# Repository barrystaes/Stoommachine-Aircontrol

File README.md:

# Stoommachine aircontrol
Stichting Stoommachine Oisterwijk 
http://destoommachine.nl/

# Licence
ISC

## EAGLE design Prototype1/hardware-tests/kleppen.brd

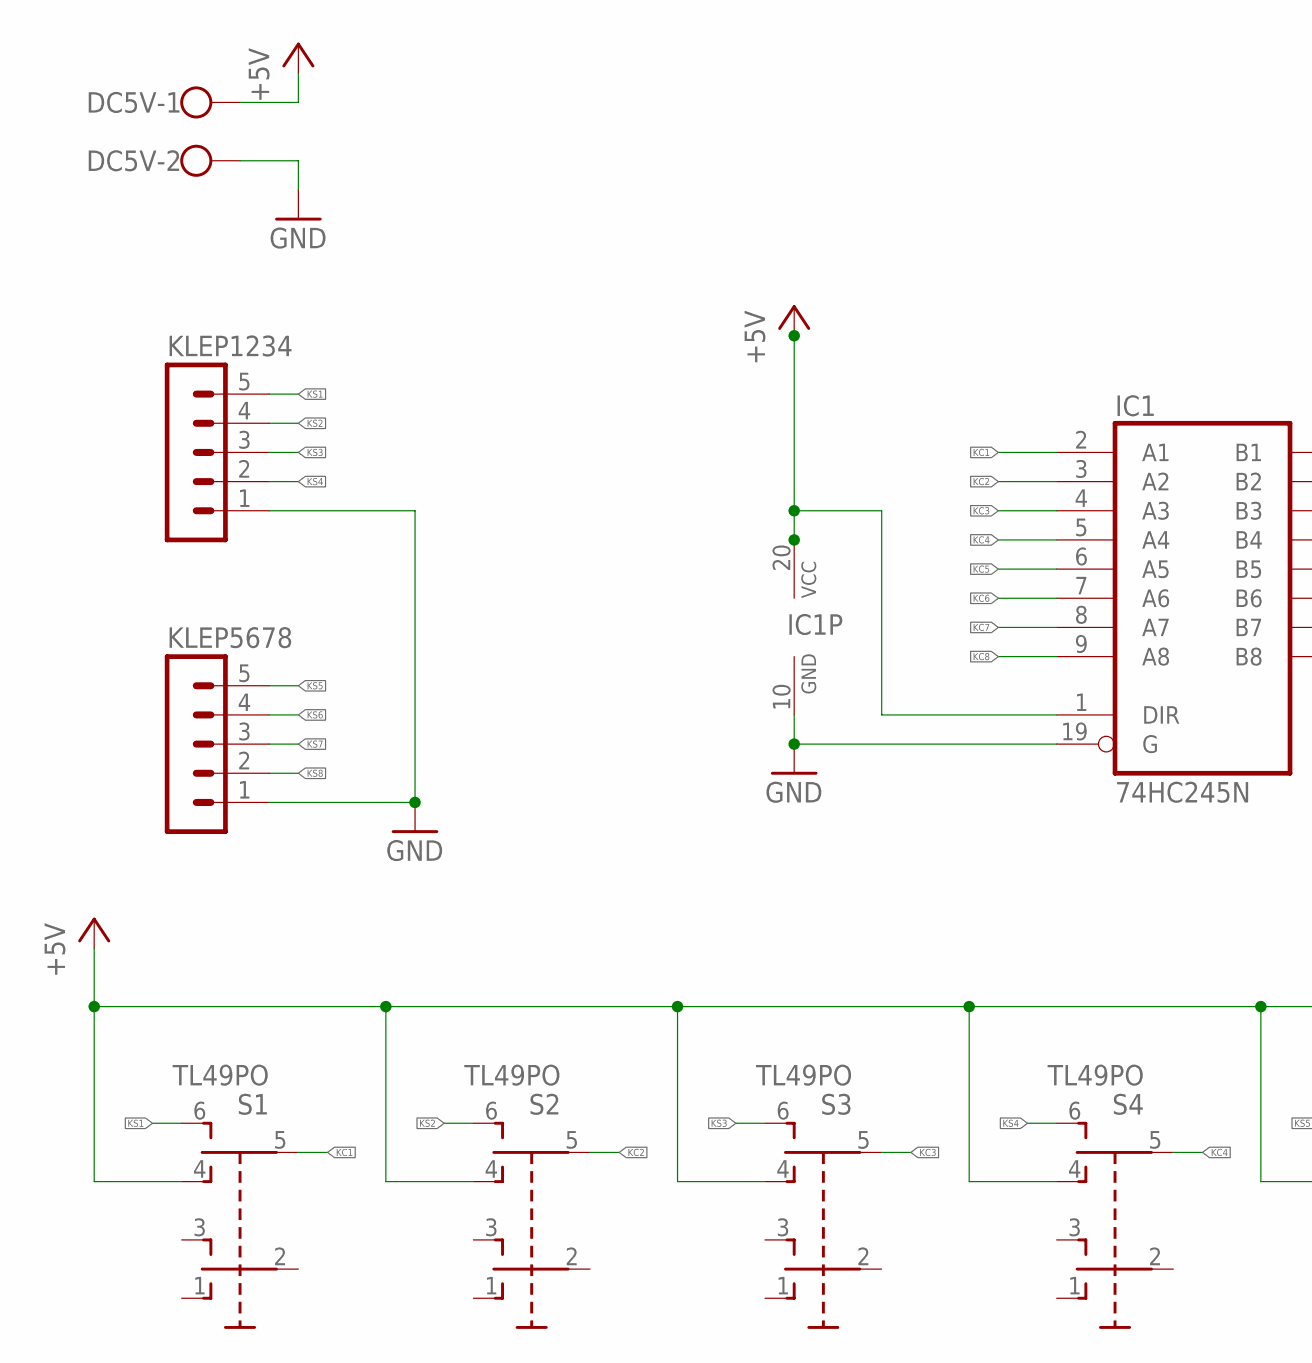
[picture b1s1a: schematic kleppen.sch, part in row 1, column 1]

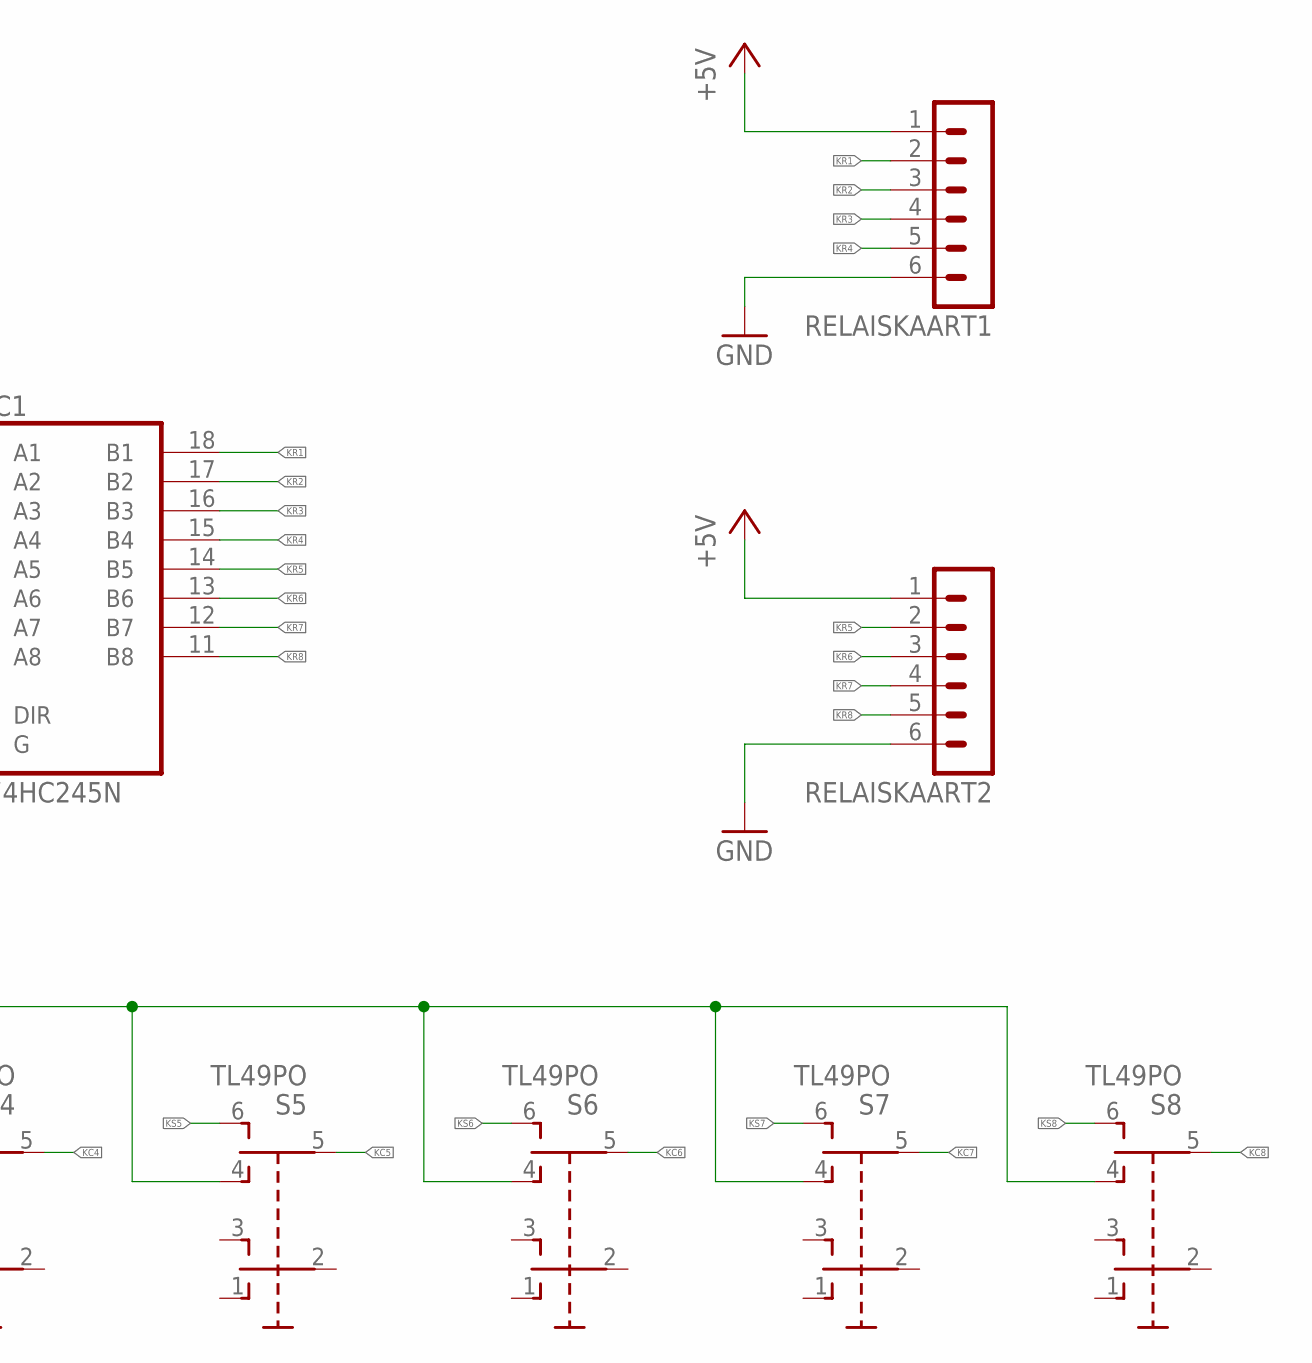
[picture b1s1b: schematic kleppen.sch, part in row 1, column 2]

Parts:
DC5V: W237-102
IC1: 74HC245N; DIL20
KLEP1234, KLEP5678: MA05-1
RELAISKAART1, RELAISKAART2: MA06-1
S1, S2, S3, S4, S5, S6, S7, S8: TL49PO; TL4XPO

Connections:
+5V: DC5V.1, IC1.1 (DIR), IC1.20 (VCC), RELAISKAART1.1, RELAISKAART2.1, S1.4 (O1), S2.4 (O1), S3.4 (O1), S4.4 (O1), S5.4 (O1), S6.4 (O1), S7.4 (O1), S8.4 (O1)
GND: DC5V.2, IC1.10 (GND), IC1.19 (G), RELAISKAART1.6, RELAISKAART2.6
KC1: IC1.2 (A1), S1.5 (P1)
KC2: IC1.3 (A2), S2.5 (P1)
KC3: IC1.4 (A3), S3.5 (P1)
KC4: IC1.5 (A4), S4.5 (P1)
KC5: IC1.6 (A5), S5.5 (P1)
KC6: IC1.7 (A6), S6.5 (P1)
KC7: IC1.8 (A7), S7.5 (P1)
KC8: IC1.9 (A8), S8.5 (P1)
KR1: IC1.18 (B1), RELAISKAART1.2
KR2: IC1.17 (B2), RELAISKAART1.3
KR3: IC1.16 (B3), RELAISKAART1.4
KR4: IC1.15 (B4), RELAISKAART1.5
KR5: IC1.14 (B5), RELAISKAART2.2
KR6: IC1.13 (B6), RELAISKAART2.3
KR7: IC1.12 (B7), RELAISKAART2.4
KR8: IC1.11 (B8), RELAISKAART2.5
KS1: KLEP1234.5, S1.6 (S1)
KS2: KLEP1234.4, S2.6 (S1)
KS3: KLEP1234.3, S3.6 (S1)
KS4: KLEP1234.2, S4.6 (S1)
KS5: KLEP5678.5, S5.6 (S1)
KS6: KLEP5678.4, S6.6 (S1)
KS7: KLEP5678.3, S7.6 (S1)
KS8: KLEP1234.1, KLEP5678.1, KLEP5678.2, S8.6 (S1)

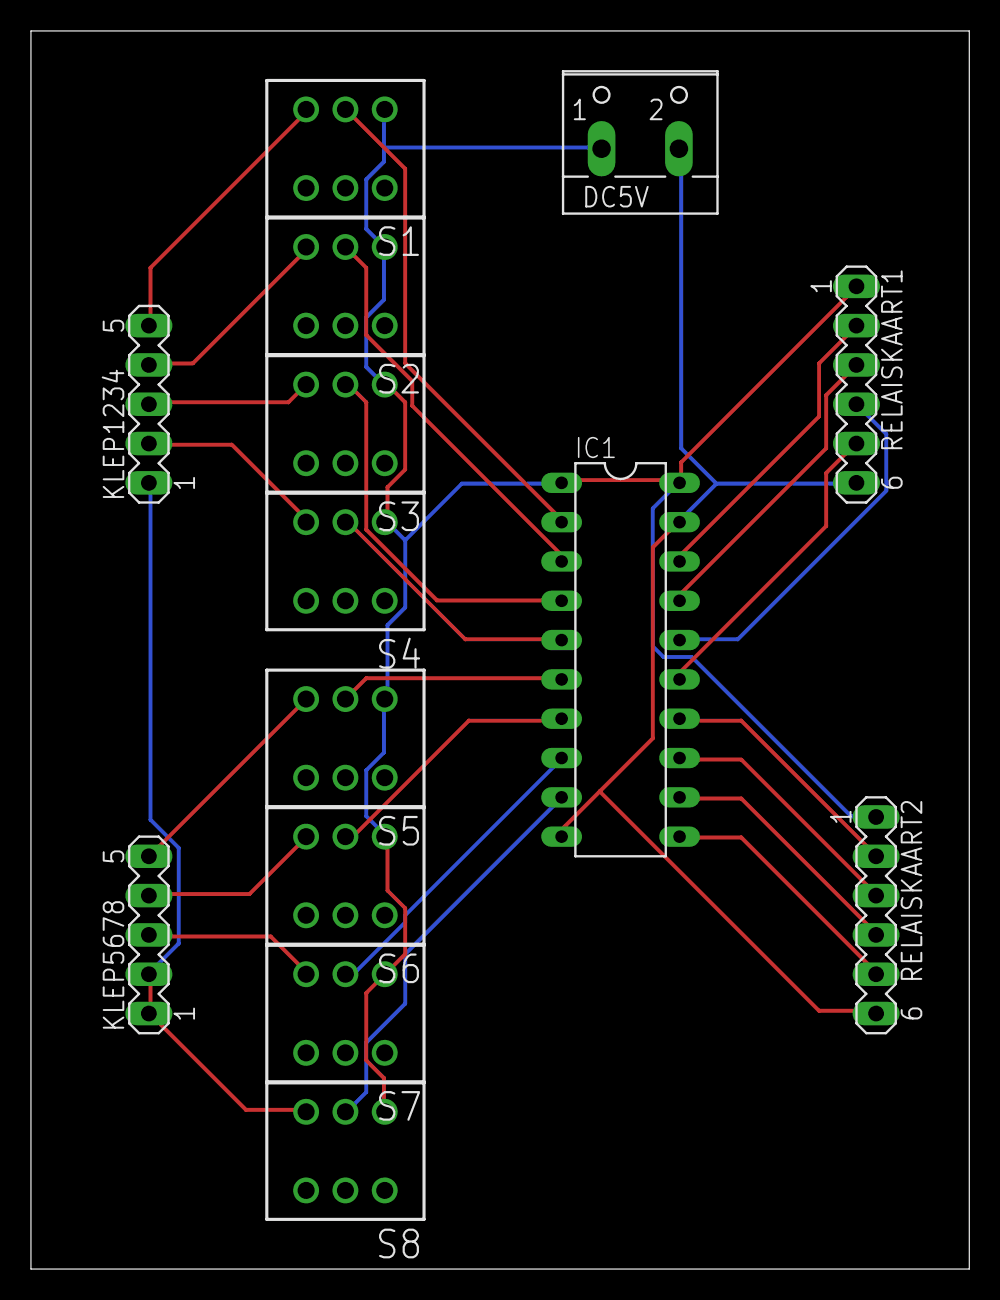
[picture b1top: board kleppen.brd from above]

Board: 2 copper layers, 60.6 x 80.0 mm, 14 parts (0 on the bottom side), 26 nets.

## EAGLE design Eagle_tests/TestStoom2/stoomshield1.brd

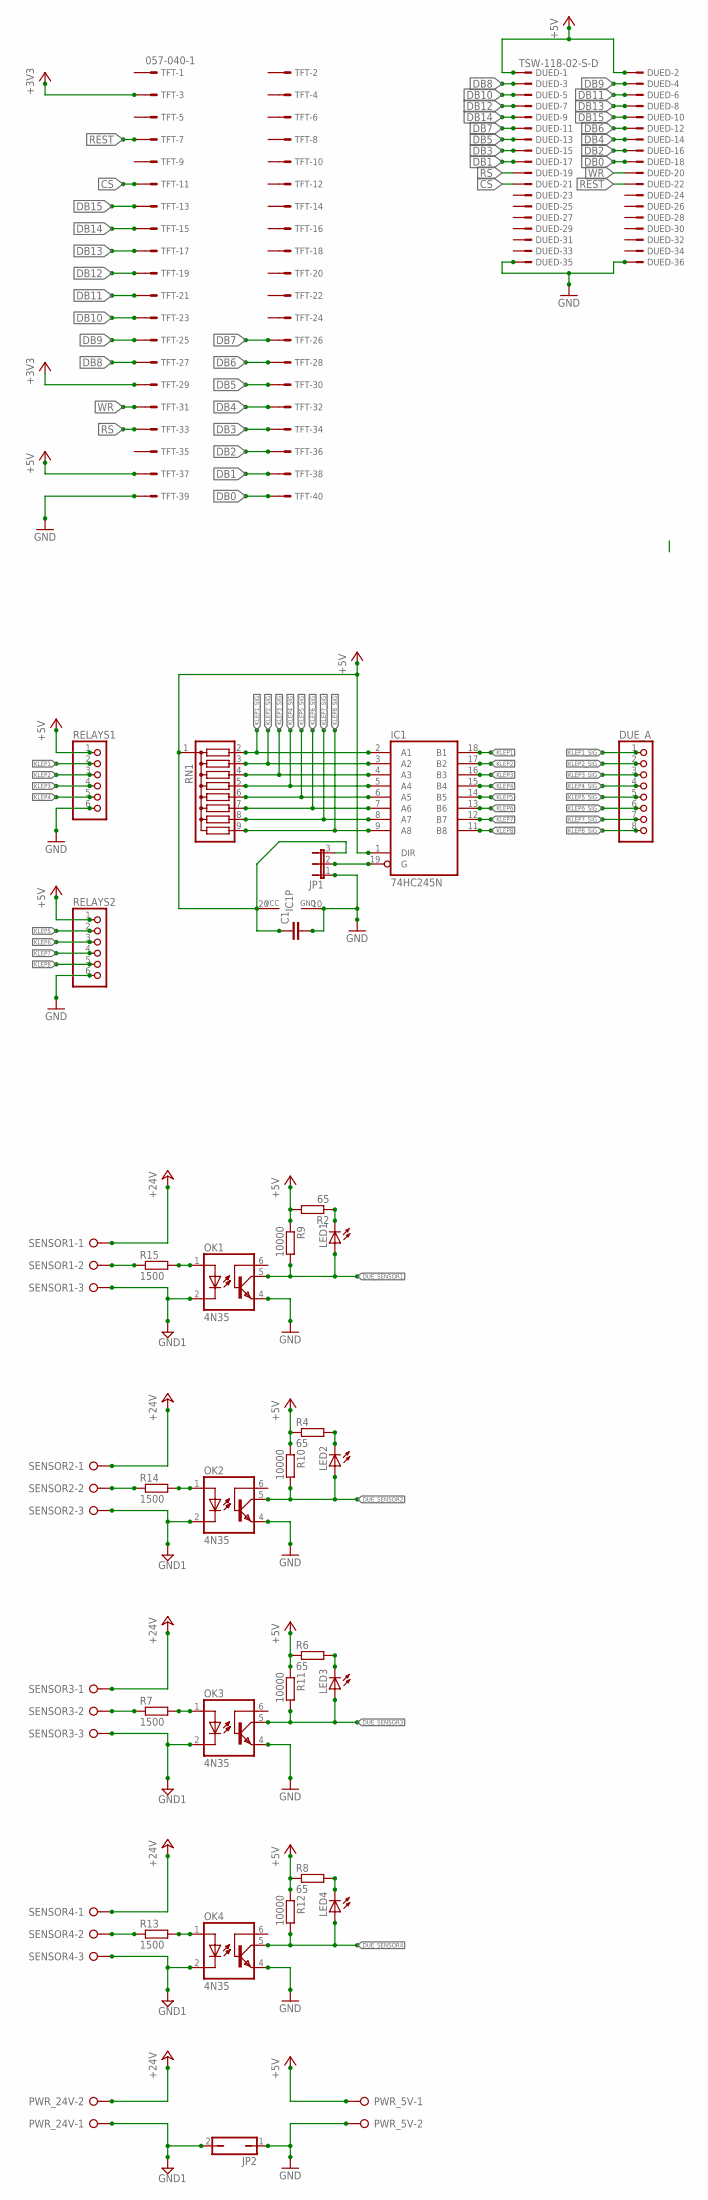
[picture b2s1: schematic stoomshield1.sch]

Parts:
C1: C-EU025-024X044; C025-024X044
DUED: TSW-118-02-S-D
DUE_A: PINHD-1X8; 1X08
IC1: 74HC245N; DIL20
JP1: JP2E; JP2
JP2: JP1Q; JP1
LED1, LED2, LED3, LED4: LED5MM
OK1, OK2, OK3, OK4: 4N35; DIL06
PWR_5V, PWR_24V: W237-02P; W237-132
R2, R4, R6, R8: 65; 0204/5
R7, R13, R14, R15: 1500; 0204/5
R9, R10, R11, R12: 10000; 0204/5
RELAYS1, RELAYS2: PINHD-1X6; 1X06
RN1: G08R; SIL9
SENSOR1, SENSOR2, SENSOR3, SENSOR4: W237-03P; W237-133
TFT: 057-040-1

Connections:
+5V: C1.1, DUED.1, DUED.2, IC1.1 (DIR), IC1.20 (VCC), JP1.3, PWR_5V.1, R2.2, R4.1, R6.1, R8.1, R9.1, R10.1, R11.1, R12.1, RELAYS1.1, RELAYS2.1, RN1.1, TFT.37
+24V: PWR_24V.2, SENSOR1.1, SENSOR2.1, SENSOR3.1, SENSOR4.1
CS: DUED.21, TFT.11
DB0: DUED.18, TFT.40
DB1: DUED.17, TFT.38
DB2: DUED.16, TFT.36
DB3: DUED.15, TFT.34
DB4: DUED.14, TFT.32
DB5: DUED.13, TFT.30
DB6: DUED.12, TFT.28
DB7: DUED.11, TFT.26
DB8: DUED.3, TFT.27
DB9: DUED.4, TFT.25
DB10: DUED.5, TFT.23
DB11: DUED.6, TFT.21
DB12: DUED.7, TFT.19
DB13: DUED.8, TFT.17
DB14: DUED.9, TFT.15
DB15: DUED.10, TFT.13
DUE_SENSOR1: LED1.A, OK1.5 (COL), R9.2
DUE_SENSOR2: LED2.A, OK2.5 (COL), R10.2
DUE_SENSOR3: LED3.A, OK3.5 (COL), R11.2
DUE_SENSOR4: LED4.A, OK4.5 (COL), R12.2
GND: C1.2, DUED.35, DUED.36, IC1.10 (GND), JP1.1, JP2.1, OK1.4 (EMI), OK2.4 (EMI), OK3.4 (EMI), OK4.4 (EMI), PWR_5V.2, RELAYS1.6, RELAYS2.6, TFT.39
GND1: JP2.2, OK1.2 (C), OK2.2 (C), OK3.2 (C), OK4.2 (C), PWR_24V.1, SENSOR1.3, SENSOR2.3, SENSOR3.3, SENSOR4.3
KLEP1: IC1.18 (B1), RELAYS1.2
KLEP1_SIG: DUE_A.1, IC1.2 (A1), RN1.2
KLEP2: IC1.17 (B2), RELAYS1.3
KLEP2_SIG: DUE_A.2, IC1.3 (A2), RN1.3
KLEP3: IC1.16 (B3), RELAYS1.4
KLEP3_SIG: DUE_A.3, IC1.4 (A3), RN1.4
KLEP4: IC1.15 (B4), RELAYS1.5
KLEP4_SIG: DUE_A.4, IC1.5 (A4), RN1.5
KLEP5: IC1.14 (B5), RELAYS2.2
KLEP5_SIG: DUE_A.5, IC1.6 (A5), RN1.6
KLEP6: IC1.13 (B6), RELAYS2.3
KLEP6_SIG: DUE_A.6, IC1.7 (A6), RN1.7
KLEP7: IC1.12 (B7), RELAYS2.4
KLEP7_SIG: DUE_A.7, IC1.8 (A7), RN1.8
KLEP8: IC1.11 (B8), RELAYS2.5
KLEP8_SIG: DUE_A.8, IC1.9 (A8), RN1.9
unnamed: IC1.19 (G), JP1.2
unnamed: R15.1, SENSOR1.2
unnamed: OK1.1 (A), R15.2
unnamed: LED1.K (C), R2.1
unnamed: OK2.1 (A), R14.2
unnamed: R14.1, SENSOR2.2
unnamed: LED2.K (C), R4.2
unnamed: OK3.1 (A), R7.2
unnamed: R7.1, SENSOR3.2
unnamed: LED3.K (C), R6.2
unnamed: OK4.1 (A), R13.2
unnamed: R13.1, SENSOR4.2
unnamed: LED4.K (C), R8.2
REST: DUED.22, TFT.7
RS: DUED.19, TFT.33
WR: DUED.20, TFT.31

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
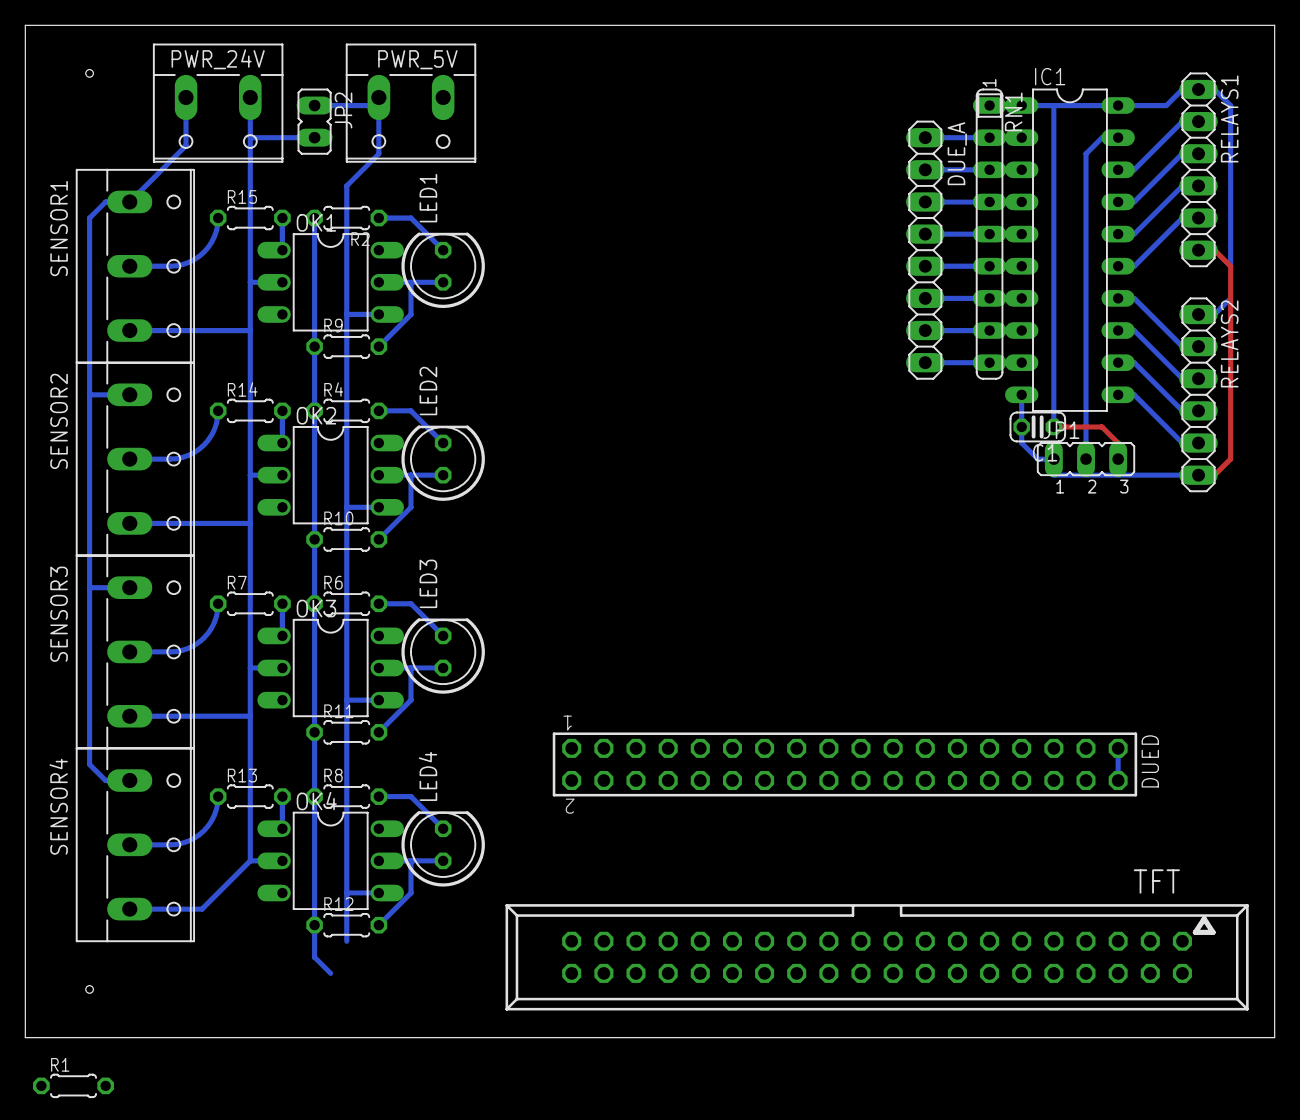
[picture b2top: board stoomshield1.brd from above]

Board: 2 copper layers, 98.7 x 80.0 mm, 37 parts (0 on the bottom side), 59 nets.

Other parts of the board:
R1: 10000; 0204/5

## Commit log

2015-02-08 Fix lcd shield test
2015-02-15 eeprom 1st pseudocode
2015-02-15 eeprom 2nd pseudocode
2015-02-15 eeprom 3nd pseudocode (todo implement test)
2015-02-15 Added loopcounter to lcd shield test
2015-02-18 Added timer-interrupt counter to lcd shield test (also serial but commented)
2015-03-01 Initial Eagle files (schema dummy test, todo pcb)
2015-03-02 LICENCE.md
2015-03-05 PCB schema test 4klep.
2015-03-26 Added UTFT demo for Arduino Due with SSD1289 tft.
2015-04-01 Changed timer-interrupt counter test to support Arduino Due + UTFT
2015-04-02 Added relay test for Arduino Due.
2015-04-02 Extended relay test for Arduino Due.
2015-04-02 Added combined test for Arduino Due.
2015-04-13 Hardware test: eagle file with TFT-Due connectors
2015-04-14 Hardware test: eagle file with TFT-Due connectors + relay buffer
2015-04-15 Added sensor readout to combined test.
2015-04-15 Hardware test: eagle file with TFT-Due connectors + relay buffer + sensor optocoupler
2015-04-17 Software test: Added sensorgraph_test.
2015-04-17 Software test: Refactored sensorgraph_test into SensorGraph library. (prep for log/render of multiple sensors)
2015-04-17 Software test: Refactored sensorgraph_test (fix background render)
2015-04-18 Software test: Refactored sensorgraph_test (custom color, render window)
2015-04-18 Software test: Now SensorGraph library can be used for multiple (seperate) graphs.
2015-04-20 Hardware test: eagle schema details
2015-04-20 Hardware test: eagle pcb mockup backup
2015-04-22 Hardware test: improved eagle pcb (100x80mm) with sensor leds.
2015-04-24 Hardware test: improved eagle pcb screw contact wiring.
2015-04-24 Hardware test: improved eagle pcb+schema for relay.
2015-04-29 Hardware test: aproximated eagle pcb TFT connector placement.
2015-06-02 Fix UTFT demo to work with prototype wiring.
2015-06-06 Software test: Updated sensorgraph_test to new hardware setup (prototype 2)
2015-06-06 Initial TODO.txt for Aircontrol.
2015-06-07 Hardware schema: Fixed RS pull-up.
2015-06-08 Docs: design document (late commit)
2015-06-08 Docs: design document v20150609 (copy from google drive)
2015-06-12 Prototype2 hardware: Reorganizing files.
2015-06-12 Prototype1 hardware: Reorganizing files.
2015-06-12 Prototype1 software: Reorganizing files.
2015-06-12 Updated TODO
2015-06-12 Prototype2 software: Initial empty Arduino project.
2015-06-12 Resources: added datasheets (late commit)
2015-06-12 Resources: added UTFT software and docs
2015-06-12 Prototype2 software: Added UTFT and test render.
2015-06-12 Prototype2 software: Now uses (quadratic encoder) sensors, shows state and keeps position.
2015-06-12 Prototype2 software: Now tracks errors + asserts.
2015-06-12 Prototype2 software: Now tracks errors + asserts for zero position.
2015-06-13 Prototype2 software: Now tracks FPS.
2015-06-13 Prototype2 software: Now calculates FPS/RPM as float. (performance hit: FPS dropped to 13 fom 20)
2015-06-13 Prototype2 software: Removed float FPS/RPM calculations. (performance gain: FPS from 13 to 14)
2015-06-13 Prototype2 software: Fixed RPM negative overflow, for now.
2015-06-15 Prototype2 software: Settings for sundays test.
2015-06-15 Prototype2: Added readme.
2015-06-20 Prototype2 software: Testing hardware/wiring change. (in preperation for reading port C)
2015-06-21 Resources: added datasheet of Arduino Due mcu.
2015-06-21 Prototype2 software: Testing reading port C.
2015-06-21 Prototype2 software: Testing portait display, for fitting graphs.
2015-06-22 Prototype2 software: Demonstrated upto 150000 measurements per second, changing from 1000 to 50000.
2015-07-05 Prototype2 software: Testing analogRead (late commit)
2015-07-05 Backup of TODO
2015-07-05 Prototype2 software: Initial RevLog test. (tested, works)
2015-07-05 Prototype2 software: Added RPM to RevLog.
2015-07-05 Prototype2 software: Added margin values to RevLog.
2015-08-08 Prototype2 software: Added rowcolors to RevLog.
2015-08-08 Prototype2 software: Added interim valveAin valveAout outputs.
2015-08-08 Prototype2 software: Fixed valveAin valveAout output pins
2015-08-15 Prototype2 software: Initial test for logging valveAin valveAout output
2015-08-15 Prototype2 software: Better valve timing.
2015-08-15 Prototype2 software: Fixed logging valveAin valveAout output
2015-08-22 Prototype2 software: Complete logging valveAin valveAout output
2015-08-22 Prototype2 software: Test valve timing. (50% trim)
2015-08-22 Prototype2 software: Test valve timing. (25% trim)
2015-08-29 Prototype2 software: Test start prerequisites: zero-sensor.
2015-08-29 Prototype2 software: Test valve timing. (test door rik)
2015-09-02 Prototype2 software: Test valve timing. (input longer, less vacuum)
2015-09-03 Prototype2 software: Test valve timing. (output shorter)
2015-09-05 Aircontrol: Initial eclipse project
2015-09-05 Aircontrol: Add green button test code
2015-09-07 Aircontrol: Initial Fouten.cpp and Fouten.h files. (not doing much)
2015-09-07 Aircontrol: Improving Fouten class. (not used yet)
2015-09-07 Aircontrol: Testing Fouten class.
2015-09-07 Aircontrol: Added redflags.GreycodeSensor to Fouten class
2015-09-07 Aircontrol: Refactored to renderScreen routines
2015-09-07 Aircontrol: Fixed tabs to eclipse editor defaults
2015-09-07 Aircontrol: Initial renderScreen_RedFlags() test
2015-09-09 Aircontrol: Enum for menupage render statemachine
2015-09-10 Aircontrol: Enum for control statemachine (bootscreen not working)
2015-09-10 Aircontrol: iets
2015-09-10 Aircontrol: iets (late commits)
2015-09-11 Aircontrol: fixed potential issue with control state
2015-09-11 Aircontrol: improved debug (and moved enum to h file because its used in function definition)
2015-09-11 Aircontrol: fixed issue with control state
2015-09-11 Aircontrol: normalized settings
2015-09-11 Aircontrol: fixed and enabled debug
2015-09-11 Aircontrol: various
2015-09-11 Aircontrol: added MyLog()
2015-09-11 Aircontrol: Completing CONTROL_RUNNING
2015-09-11 Aircontrol: Fixed GRAPH screen.
2015-09-11 Aircontrol: Better GRAPH screen layout
2015-09-11 Aircontrol: Made ReverseRPM and OverspeedRPM redflags sticky. Requires reboot.
2015-09-11 Aircontrol: Connected more ESTOP contacts.
2015-09-11 Aircontrol: Fixed motor ESTOP contacts.
2015-09-11 Aircontrol: Fixed start position indication
2015-09-12 Aircontrol: Fixed initial relay states. And both valves now wired to their respective NO (normally-open) contacts.
2016-02-04 Toevoegen overdruk sensor. (compileert maar nog niet aangelsoten of getest)
2016-03-12 Aansluiten overdruk sensor. (nog niet getest)
2016-08-27 Aircontrol: New valve timing. (late commit, 2015-05-02)
2016-11-02 Aircontrol: Fixed Overdruk readout. (tested with John+Jo+Barry, working OK, sensor set to 7 bar)
2017-02-04 Simulatie wiel instellingen (niet getest)
2017-02-04 Simulatie wiel instellingen (fixed, tested OK)
2017-02-04 Altijd debug pagina in beeld tonen.
2017-02-04 Testcode met geinverteerde ValveAout in writeOutputs() en debug output. (sturing loopt vast? laptop voeding?)
2017-02-10 Documentatie update: pinout op Arduino Due sturing
2017-02-11 Testcode met normale valveAout, zonder debug output (dat gaf crash bij opstarten)
2017-02-11 Testcode met omgedraaide valveAout start/stop en omgekeerde (normaly-open) relais contacten
2017-02-11 Testcode met omgedraaide valveAout start/stop en omgekeerde (normaly-open) relais contacten + omgekeerde overdruk sensor
2017-02-11 Testcode met (beter) omgedraaide valveAout start/stop (in plaats van 0)
2018-02-10 Nette versie 2017, revisie 1, schemas
2018-02-10 Nette versie 2017, revisie 1, software (kopie van eclipse project \Prototype2\software\eclipse\stoomshield_prototype2\ )
2018-02-10 Nette versie 2017, revisie 2, software: 2017-06-14 Barry: nieuwe in-outputs
2018-02-10 Nette versie 2017, revisie 3, software: 2017-06-15 John - werkende encoders
2018-02-10 Nette versie 2017, revisie 4, software: 2017-06-18 John - menuknop debug
2018-02-10 Nette versie 2017, revisie 5, software: 2017-06-19 John+Barry: geinverteerde nul en elektrische aandrijfing
2018-02-10 Nette versie 2017, revisie 6, software: 2018-02-03 John: inverteren nulsensor
2018-03-10 Nieuwe kleptiming door Rik, met nieuwe compressor.
2018-03-10 Definitieve kleptiming door Rik, met nieuwe compressor.
2021-10-20 Nieuwe kleptiming door Bas+John+Barry, finetune op gehoor (20 okt 2021)
2022-05-21 Workaround toegevoegd om Zero-Sensor Errors te resetten terwijl de machine draait.
2022-05-21 Update changelog
